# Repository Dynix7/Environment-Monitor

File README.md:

# Environment-Monitor
This is a board that serves as an environment sensor, recording the temperature, humidity, air pressure, brightness, and air quality of the area around it. It does this through the use of 5 sensors: TMP102AIDR, AHT20-F, BMP388, LTR303, and AGS10. The information can be displayed of the built in SSD1306 0.91 screen.
# Why I Made It
Not surprisingly I spend a lot of time sitting indoors in my room on my computer.  With this, I often have my door closed and sometimes the window open. I wanted a device that can monitor my room so I can make optimize my environment so if it detects that it's getting to hot (for example) I can open the window more or open my door. 

# Pictures

# BOM
|Name             |Purpose                           |Quantity|Total Cost (USD)|Link                                                                                                                                                            |Distributor|
|-----------------|----------------------------------|--------|----------------|----------------------------------------------------------------------------------------------------------------------------------------------------------------|-----------|
|3.7v Battery     |Power when not plugged in         |        |6.57            |https://www.aliexpress.us/item/3256811644617885.html                                                                                                            |Aliexpress |
|SSD1306 Display  |Displaying Measured Stats         |        |2.20            |https://www.aliexpress.us/item/3256808453793642.html                                                                                                            |Aliexpress |
|JST Connector    |Battery Connector                 |        |0.67            |https://www.lcsc.com/product-detail/C131337.html                                                                                                                |LCSC       |
|USB C Receptacle |Programming and Power             |        |0.41            |https://www.lcsc.com/product-detail/C2988369.html                                                                                                               |LCSC       |
|4.3k Resistor    |Configuration Resistor            |        |0.11            |https://www.lcsc.com/product-detail/C2930099.html                                                                                                               |LCSC       |
|62k Resistor     |Configuration Resistor            |        |0.11            |https://www.lcsc.com/product-detail/C2907059.html                                                                                                               |LCSC       |
|3k Resistor      |Configuration Resistor For BQ24075|        |0.12            |https://www.lcsc.com/product-detail/C2907033.html?spm=wm.gwc.xh.16.cbm___wm.sy.ssl.gwc&lcsc_vid=RwcIBQFURFlfBFxQFVkMX1dSRQULAgZfRVYKU1FXQQIxVlNRTlNaXlJSR1dXUDtW|LCSC       |
|2.2k Resistor    |I2C Pullups                       |        |0.10            |https://www.lcsc.com/product-detail/C2907117.html                                                                                                               |LCSC       |
|1k Resistor      |For LEDs                          |        |0.10            |https://www.lcsc.com/product-detail/C2907002.html                                                                                                               |LCSC       |
|10k Resistor     |Pull Ups                          |        |0.10            |https://www.lcsc.com/product-detail/C2930027.html?spm=wm.gwc.xh.13.cbm___wm.sy.ssl.gwc&lcsc_vid=RwcIBQFURFlfBFxQFVkMX1dSRQULAgZfRVYKU1FXQQIxVlNRTlNaXlJSR1dXUDtW|LCSC       |
|5.1k Resistor    |For USB CC1 and CC2               |        |0.10            |https://www.lcsc.com/product-detail/C2907114.html?spm=wm.gwc.xh.12.cbm___wm.sy.ssl.gwc&lcsc_vid=RwcIBQFURFlfBFxQFVkMX1dSRQULAgZfRVYKU1FXQQIxVlNRTlNaXlJSR1dXUDtW|LCSC       |
|4.7uF Capacitor  |Decoupling Capacitor              |        |0.30            |https://www.lcsc.com/product-detail/C8032.html                                                                                                                  |LCSC       |
|100nF Resistor   |Decoupling                        |        |0.25            |https://www.lcsc.com/product-detail/C5137636.html                                                                                                               |LCSC       |
|USBLC6-2SC6      |Protection for USB                |        |0.16            |https://www.lcsc.com/product-detail/C5261088.html                                                                                                               |LCSC       |
|BQ24075RGTR      |Power Path and Battery Charging   |        |1.05            |https://www.lcsc.com/product-detail/C15464.html                                                                                                                 |LCSC       |
|TPAP2112K-3.0TRG1|Power Regulator for AGS10         |        |0.35            |https://www.lcsc.com/product-detail/C23380903.html                                                                                                              |LCSC       |
|AMS1117-3.3      |Power Regulator                   |        |0.42            |https://www.lcsc.com/product-detail/C347222.html                                                                                                                |LCSC       |
|LTR-303ALS-01    |Light Sensor                      |        |0.41            |https://www.lcsc.com/product-detail/C364577.html                                                                                                                |LCSC       |
|AGS10            |TVOC/Air Quality Sensor           |        |1.59            |https://www.lcsc.com/product-detail/C3012632.html                                                                                                               |LCSC       |
|BMP388           |Air Pressure Sensor               |        |2.81            |https://www.lcsc.com/product-detail/C779278.html                                                                                                                |LCSC       |
|TMP102AIDRLR     |Accurate Temperature Sensor       |        |1.27            |https://www.lcsc.com/product-detail/C99269.html                                                                                                                 |LCSC       |
|AHT20-F          |Humidity Sensor                   |1       |0.76            |https://www.lcsc.com/product-detail/C3012622.html                                                                                                               |LCSC       |
|ESP32-S3         |Microcontroller for board         |1       |5.25            |https://www.lcsc.com/product-detail/C2913205.html                                                                                                               |LCSC       |
|Stencil          |Help With Soldering               |        |7.11            |                                                                                                                                                                |JLCPCB     |
|PCB              |Place Components On               |        |5.11            |                                                                                                                                                                |JLCPCB     |

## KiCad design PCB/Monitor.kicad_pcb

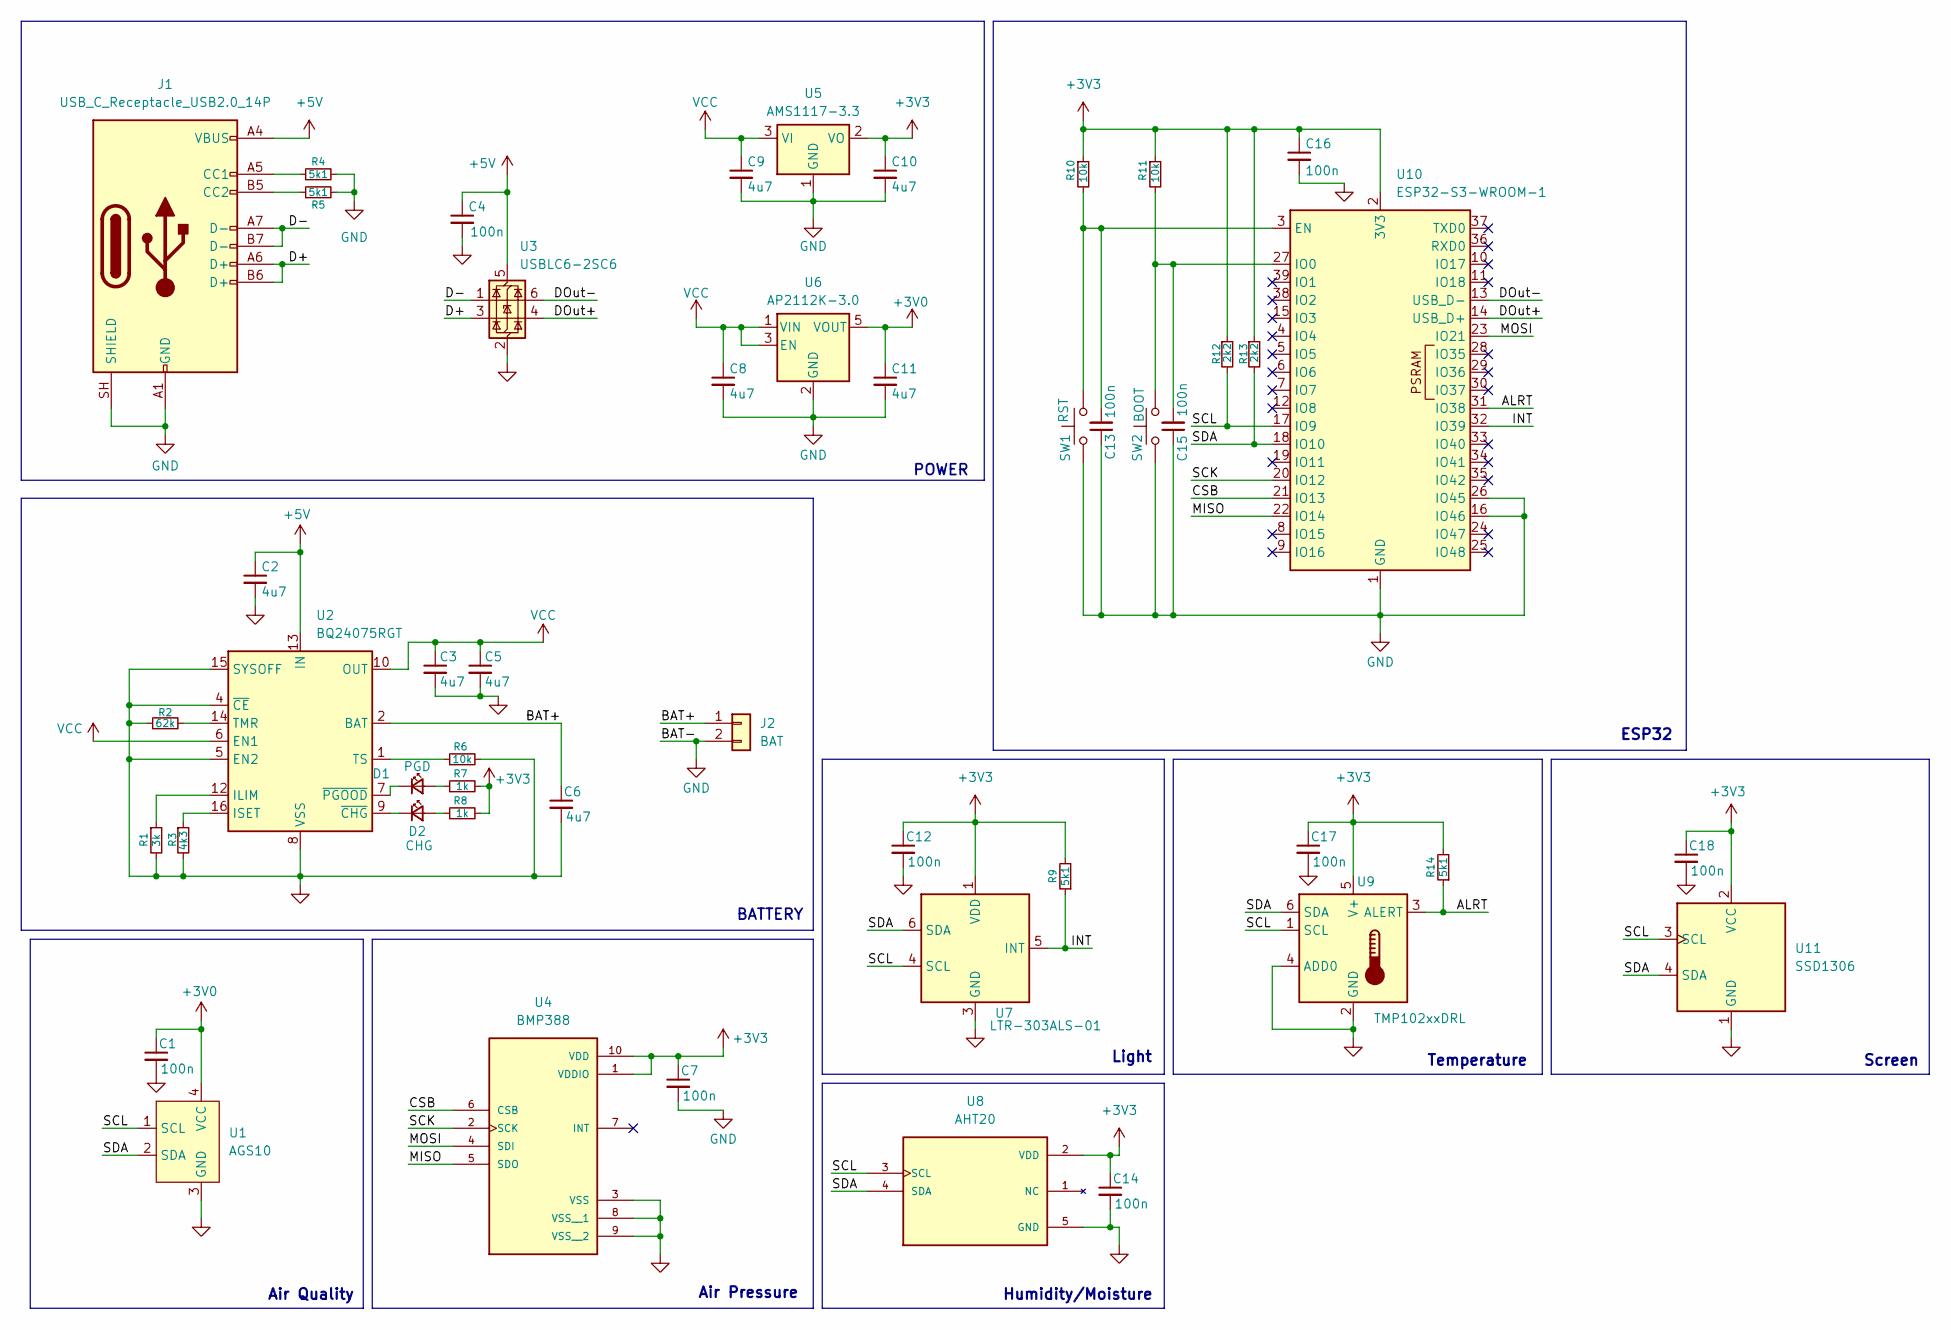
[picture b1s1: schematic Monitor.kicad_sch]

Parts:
C1, C4, C7, C12, C13, C14, C15, C16, C17, C18: 100n; C_0603_1608Metric
C2, C3, C5, C6, C8, C9, C10, C11: 4u7; C_0603_1608Metric
D1: PGD; LED_1206_3216Metric
D2: CHG; LED_1206_3216Metric
J1: USB_C_Receptacle_USB2.0_14P; USB_C_Receptacle_G-Switch_GT-USB-7010ASV
J2: BAT; JST_PH_B2B-PH-K_1x02_P2.00mm_Vertical
R1: 3k; R_0603_1608Metric
R2: 62k; R_0603_1608Metric
R3: 4k3; R_0603_1608Metric
R4, R5, R9, R14: 5k1; R_0603_1608Metric
R6, R10, R11: 10k; R_0603_1608Metric
R7, R8: 1k; R_0603_1608Metric
R12, R13: 2k2; R_0603_1608Metric
SW1: RST; SW_SPST_PTS647_Sx38
SW2: BOOT; SW_SPST_PTS647_Sx38
U1: AGS10
U2: BQ24075RGT; VQFN-16-1EP_3x3mm_P0.5mm_EP1.6x1.6mm
U3: USBLC6-2SC6; SOT-23-6
U4: BMP388; XDCR_BMP388; PARTREV 1.7
U5: AMS1117-3.3; SOT-223-3_TabPin2
U6: AP2112K-3.0; SOT-23-5
U7: LTR-303ALS-01; Lite-On_LTR-303ALS-01
U8: AHT20; PSON100P300X300X110-6N; PARTREV V1.0
U9: TMP102xxDRL; SOT-563
U10: ESP32-S3-WROOM-1
U11: SSD1306; ER_OLEDM0.91_1x-I2C

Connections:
+3V0: C1.1, C11.1, U1.4 (VCC), U6.5 (VOUT)
+3V3: C7.1, C10.1, C12.1, C14.1, C16.1, C17.1, C18.1, R7.2, R8.2, R9.2, R10.1, R11.1, R12.1, R13.1, R14.2, U4.1 (VDDIO), U4.10 (VDD), U5.2 (VO), U7.1 (VDD), U8.2 (VDD), U9.5 (V+), U10.2 (3V3), U11.2 (VCC)
+5V: C2.1, C4.1, J1.A4 (VBUS), J1.A9 (VBUS), J1.B4 (VBUS), J1.B9 (VBUS), U2.13 (IN), U3.5 (VBUS)
/ALRT: R14.1, U9.3 (ALERT), U10.31 (IO38)
/BAT+: C6.1, J2.1, U2.2 (BAT), U2.3 (BAT)
/CSB: U4.6 (CSB), U10.21 (IO13)
/D+: J1.A6 (D+), J1.B6 (D+), U3.3 (I/O2)
/D-: J1.A7 (D-), J1.B7 (D-), U3.1 (I/O1)
/DOut+: U3.4 (I/O2), U10.14 (USB_D+)
/DOut-: U3.6 (I/O1), U10.13 (USB_D-)
/INT: R9.1, U7.5 (INT), U10.32 (IO39)
/MISO: U4.5 (SDO), U10.22 (IO14)
/MOSI: U4.4 (SDI), U10.23 (IO21)
/SCK: U4.2 (SCK), U10.20 (IO12)
/SCL: R12.2, U1.1 (SCL), U7.4 (SCL), U8.3 (SCL), U9.1 (SCL), U10.17 (IO9), U11.3 (SCL)
/SDA: R13.2, U1.2 (SDA), U7.6 (SDA), U8.4 (SDA), U9.6 (SDA), U10.18 (IO10), U11.4 (SDA)
GND: C1.2, C2.2, C3.2, C4.2, C5.2, C6.2, C7.2, C8.2, C9.2, C10.2, C11.2, C12.2, C13.1, C14.2, C15.1, C16.2, C17.2, C18.2, J1.A1 (GND), J1.A12 (GND), J1.B1 (GND), J1.B12 (GND), J1.SH (SHIELD), J2.2, R1.2, R2.1, R3.2, R4.2, R5.2, R6.2, SW1.1, SW2.1, U1.3 (GND), U2.4 (~CE), U2.5 (EN2), U2.8 (VSS), U2.15 (SYSOFF), U2.17 (VSS), U3.2 (GND), U4.3 (VSS), U4.8 (VSS__1), U4.9 (VSS__2), U5.1 (GND), U6.2 (GND), U7.3 (GND), U8.5 (GND), U9.2 (GND), U9.4 (ADD0), U10.1 (GND), U10.16 (IO46), U10.26 (IO45), U10.40 (GND), U10.41 (GND), U11.1 (GND)
unnamed: D1.2 (A), R7.1
unnamed: D1.1 (K), U2.7 (~PGOOD)
unnamed: D2.2 (A), R8.1
unnamed: D2.1 (K), U2.9 (~CHG)
unnamed: J1.A5 (CC1), R4.1
unnamed: J1.B5 (CC2), R5.1
unnamed: R1.1, U2.12 (ILIM)
unnamed: R3.1, U2.16 (ISET)
unnamed: R2.2, U2.14 (TMR)
unnamed: R6.1, U2.1 (TS)
unnamed: C13.2, R10.2, SW1.2, U10.3 (EN)
unnamed: C15.2, R11.2, SW2.2, U10.27 (IO0)
VCC: C3.1, C5.1, C8.1, C9.1, U2.6 (EN1), U2.10 (OUT), U2.11 (OUT), U5.3 (VI), U6.1 (VIN), U6.3 (EN)

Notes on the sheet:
Screen
Humidity/Moisture
Light
Air Pressure
ESP32
Air Quality
POWER
BATTERY
Temperature

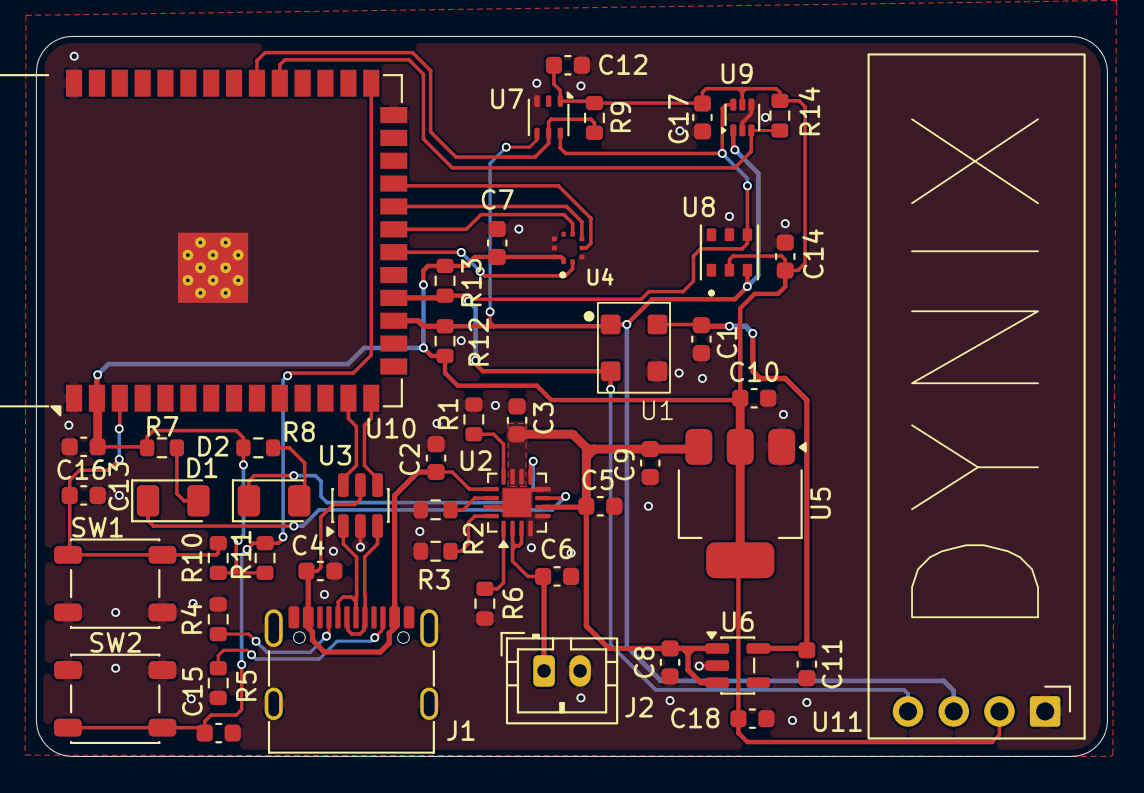
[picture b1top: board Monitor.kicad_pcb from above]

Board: 2 copper layers, 59.5 x 40.0 mm, 49 parts (0 on the bottom side), 30 nets.

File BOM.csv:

Name,Purpose,Quantity,Total Cost (USD),Link,Distributor
"3.7v Battery","Power when not plugged in",,6.57,"https://www.aliexpress.us/item/3256811644617885.html","Aliexpress"
"SSD1306 Display","Displaying Measured Stats",,2.20,"https://www.aliexpress.us/item/3256808453793642.html","Aliexpress"
"JST Connector ","Battery Connector",,0.67,"https://www.lcsc.com/product-detail/C131337.html","LCSC"
"USB C Receptacle","Programming and Power",,0.41,"https://www.lcsc.com/product-detail/C2988369.html","LCSC"
"4.3k Resistor ","Configuration Resistor",,0.11,"https://www.lcsc.com/product-detail/C2930099.html","LCSC"
"62k Resistor","Configuration Resistor",,0.11,"https://www.lcsc.com/product-detail/C2907059.html","LCSC"
"3k Resistor","Configuration Resistor For BQ24075",,0.12,"https://www.lcsc.com/product-detail/C2907033.html?spm=wm.gwc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","LCSC"
"2.2k Resistor","I2C Pullups",,0.10,"https://www.lcsc.com/product-detail/C2907117.html","LCSC"
"1k Resistor","For LEDs",,0.10,"https://www.lcsc.com/product-detail/C2907002.html","LCSC"
"10k Resistor","Pull Ups",,0.10,"https://www.lcsc.com/product-detail/C2930027.html?spm=wm.gwc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","LCSC"
"5.1k Resistor","For USB CC1 and CC2",,0.10,"https://www.lcsc.com/product-detail/C2907114.html?spm=wm.gwc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","LCSC"
"4.7uF Capacitor","Decoupling Capacitor",,0.30,"https://www.lcsc.com/product-detail/C8032.html","LCSC"
"100nF Resistor","Decoupling",,0.25,"https://www.lcsc.com/product-detail/C5137636.html","LCSC"
"USBLC6-2SC6","Protection for USB",,0.16,"https://www.lcsc.com/product-detail/C5261088.html","LCSC"
"BQ24075RGTR","Power Path and Battery Charging",,1.05,"https://www.lcsc.com/product-detail/C15464.html","LCSC"
"TPAP2112K-3.0TRG1","Power Regulator for AGS10",,0.35,"https://www.lcsc.com/product-detail/C23380903.html","LCSC"
"AMS1117-3.3","Power Regulator",,0.42,"https://www.lcsc.com/product-detail/C347222.html","LCSC"
"LTR-303ALS-01","Light Sensor",,0.41,"https://www.lcsc.com/product-detail/C364577.html","LCSC"
"AGS10","TVOC/Air Quality Sensor",,1.59,"https://www.lcsc.com/product-detail/C3012632.html","LCSC"
"BMP388","Air Pressure Sensor",,2.81,"https://www.lcsc.com/product-detail/C779278.html","LCSC"
"TMP102AIDRLR","Accurate Temperature Sensor",,1.27,"https://www.lcsc.com/product-detail/C99269.html","LCSC"
"AHT20-F","Humidity Sensor",1,0.76,"https://www.lcsc.com/product-detail/C3012622.html","LCSC"
"ESP32-S3","Microcontroller for board",1,5.25,"https://www.lcsc.com/product-detail/C2913205.html","LCSC"
"Stencil","Help With Soldering",,7.11,"","JLCPCB"
"PCB","Place Components On",,5.11,"","JLCPCB"

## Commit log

2026-05-09 Start of Schematic
2026-05-09 Most of Schematic
2026-05-11 Finish PCB + pictures + BOM
2026-05-20 Update BOM and better labeling
2026-05-20 Change .gitignore that ignored my BOM
2026-06-10 Added Firmware
2026-06-12 Add Schmatic Image and duplicated gerber file for root
